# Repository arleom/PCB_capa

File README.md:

# PCB_capa
pcb para leer ls-9000

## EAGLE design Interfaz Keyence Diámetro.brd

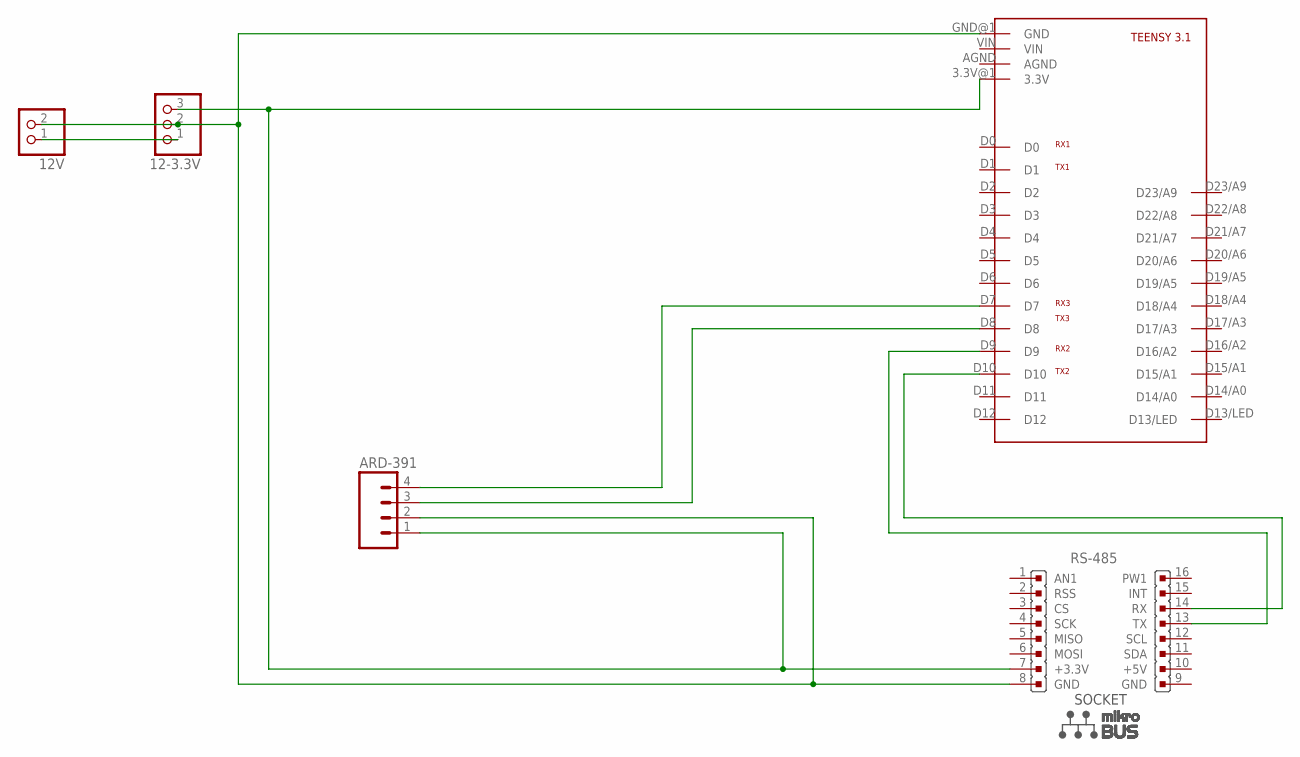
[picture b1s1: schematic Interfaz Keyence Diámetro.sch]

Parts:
12-3.3V: HEADER-1X3ROUND; 1X03_ROUND
12V: HEADER-1X2ROUND; 1X02_ROUND
ARD-391: M04NO_SILK_ALL_ROUND; 1X04_NO_SILK_ALL_ROUND
RS-485: MIKROBUS
U$1: TEENSY3.1_FRONT; TEENSY3.1_ALL

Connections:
unnamed: 12-3.3V.1, 12V.1
unnamed: 12-3.3V.2, 12V.2, ARD-391.2, RS-485.8 (GND), U$1.GND@1 (GND)
unnamed: 12-3.3V.3, ARD-391.1, RS-485.7 (+3.3V), U$1.3.3V@1 (3.3V)
unnamed: ARD-391.4, U$1.D7
unnamed: ARD-391.3, U$1.D8
unnamed: RS-485.13 (TX), U$1.D9
unnamed: RS-485.14 (RX), U$1.D10

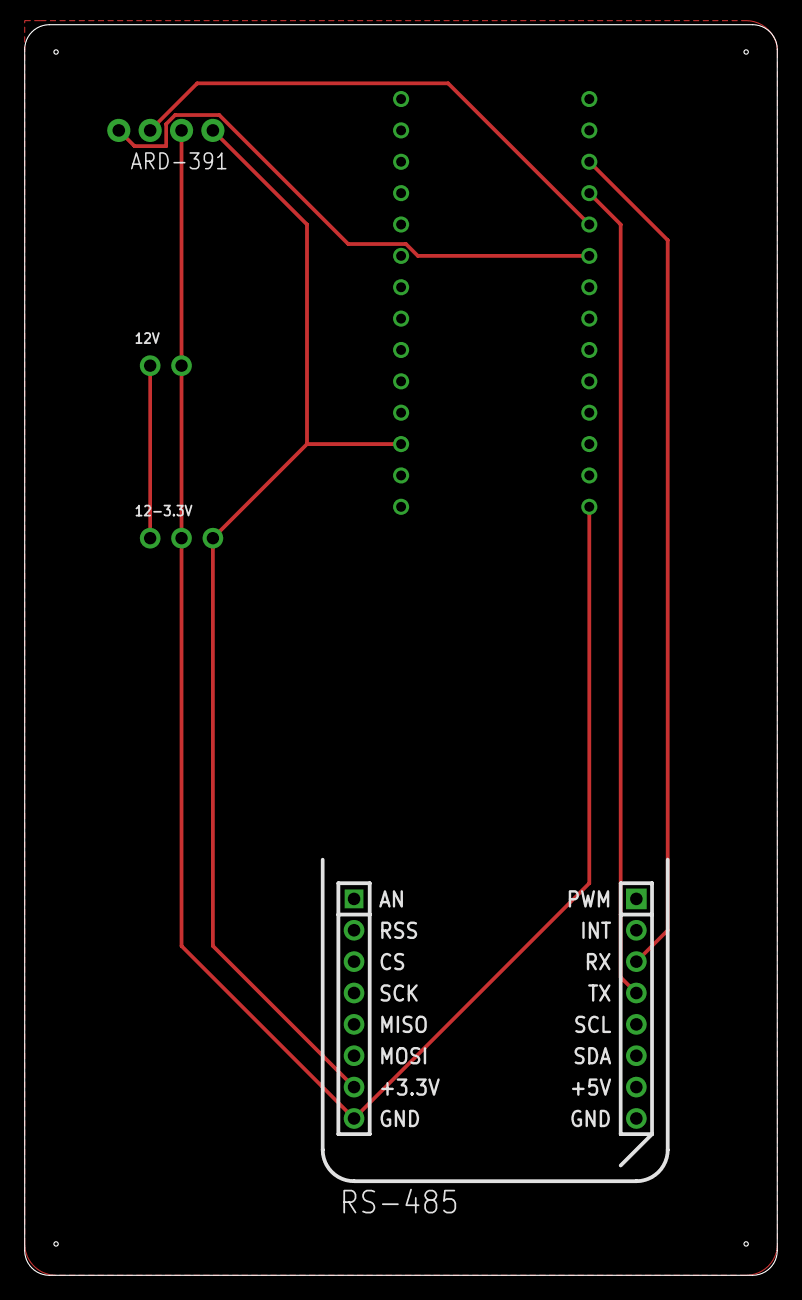
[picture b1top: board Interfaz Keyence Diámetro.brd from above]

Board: 2 copper layers, 60.9 x 101.3 mm, 5 parts (0 on the bottom side), 7 nets.

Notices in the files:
parts and their libraries:
microbuilder: This work is placed in the public domain, and may be freely used for commercial and non-commercial work with the following conditions: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
SparkFun-Connectors: Licensing: Creative Commons ShareAlike 4.0 International - https://creativecommons.org/licenses/by-sa/4.0
